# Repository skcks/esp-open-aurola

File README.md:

# esp-open-aurola
light controller board

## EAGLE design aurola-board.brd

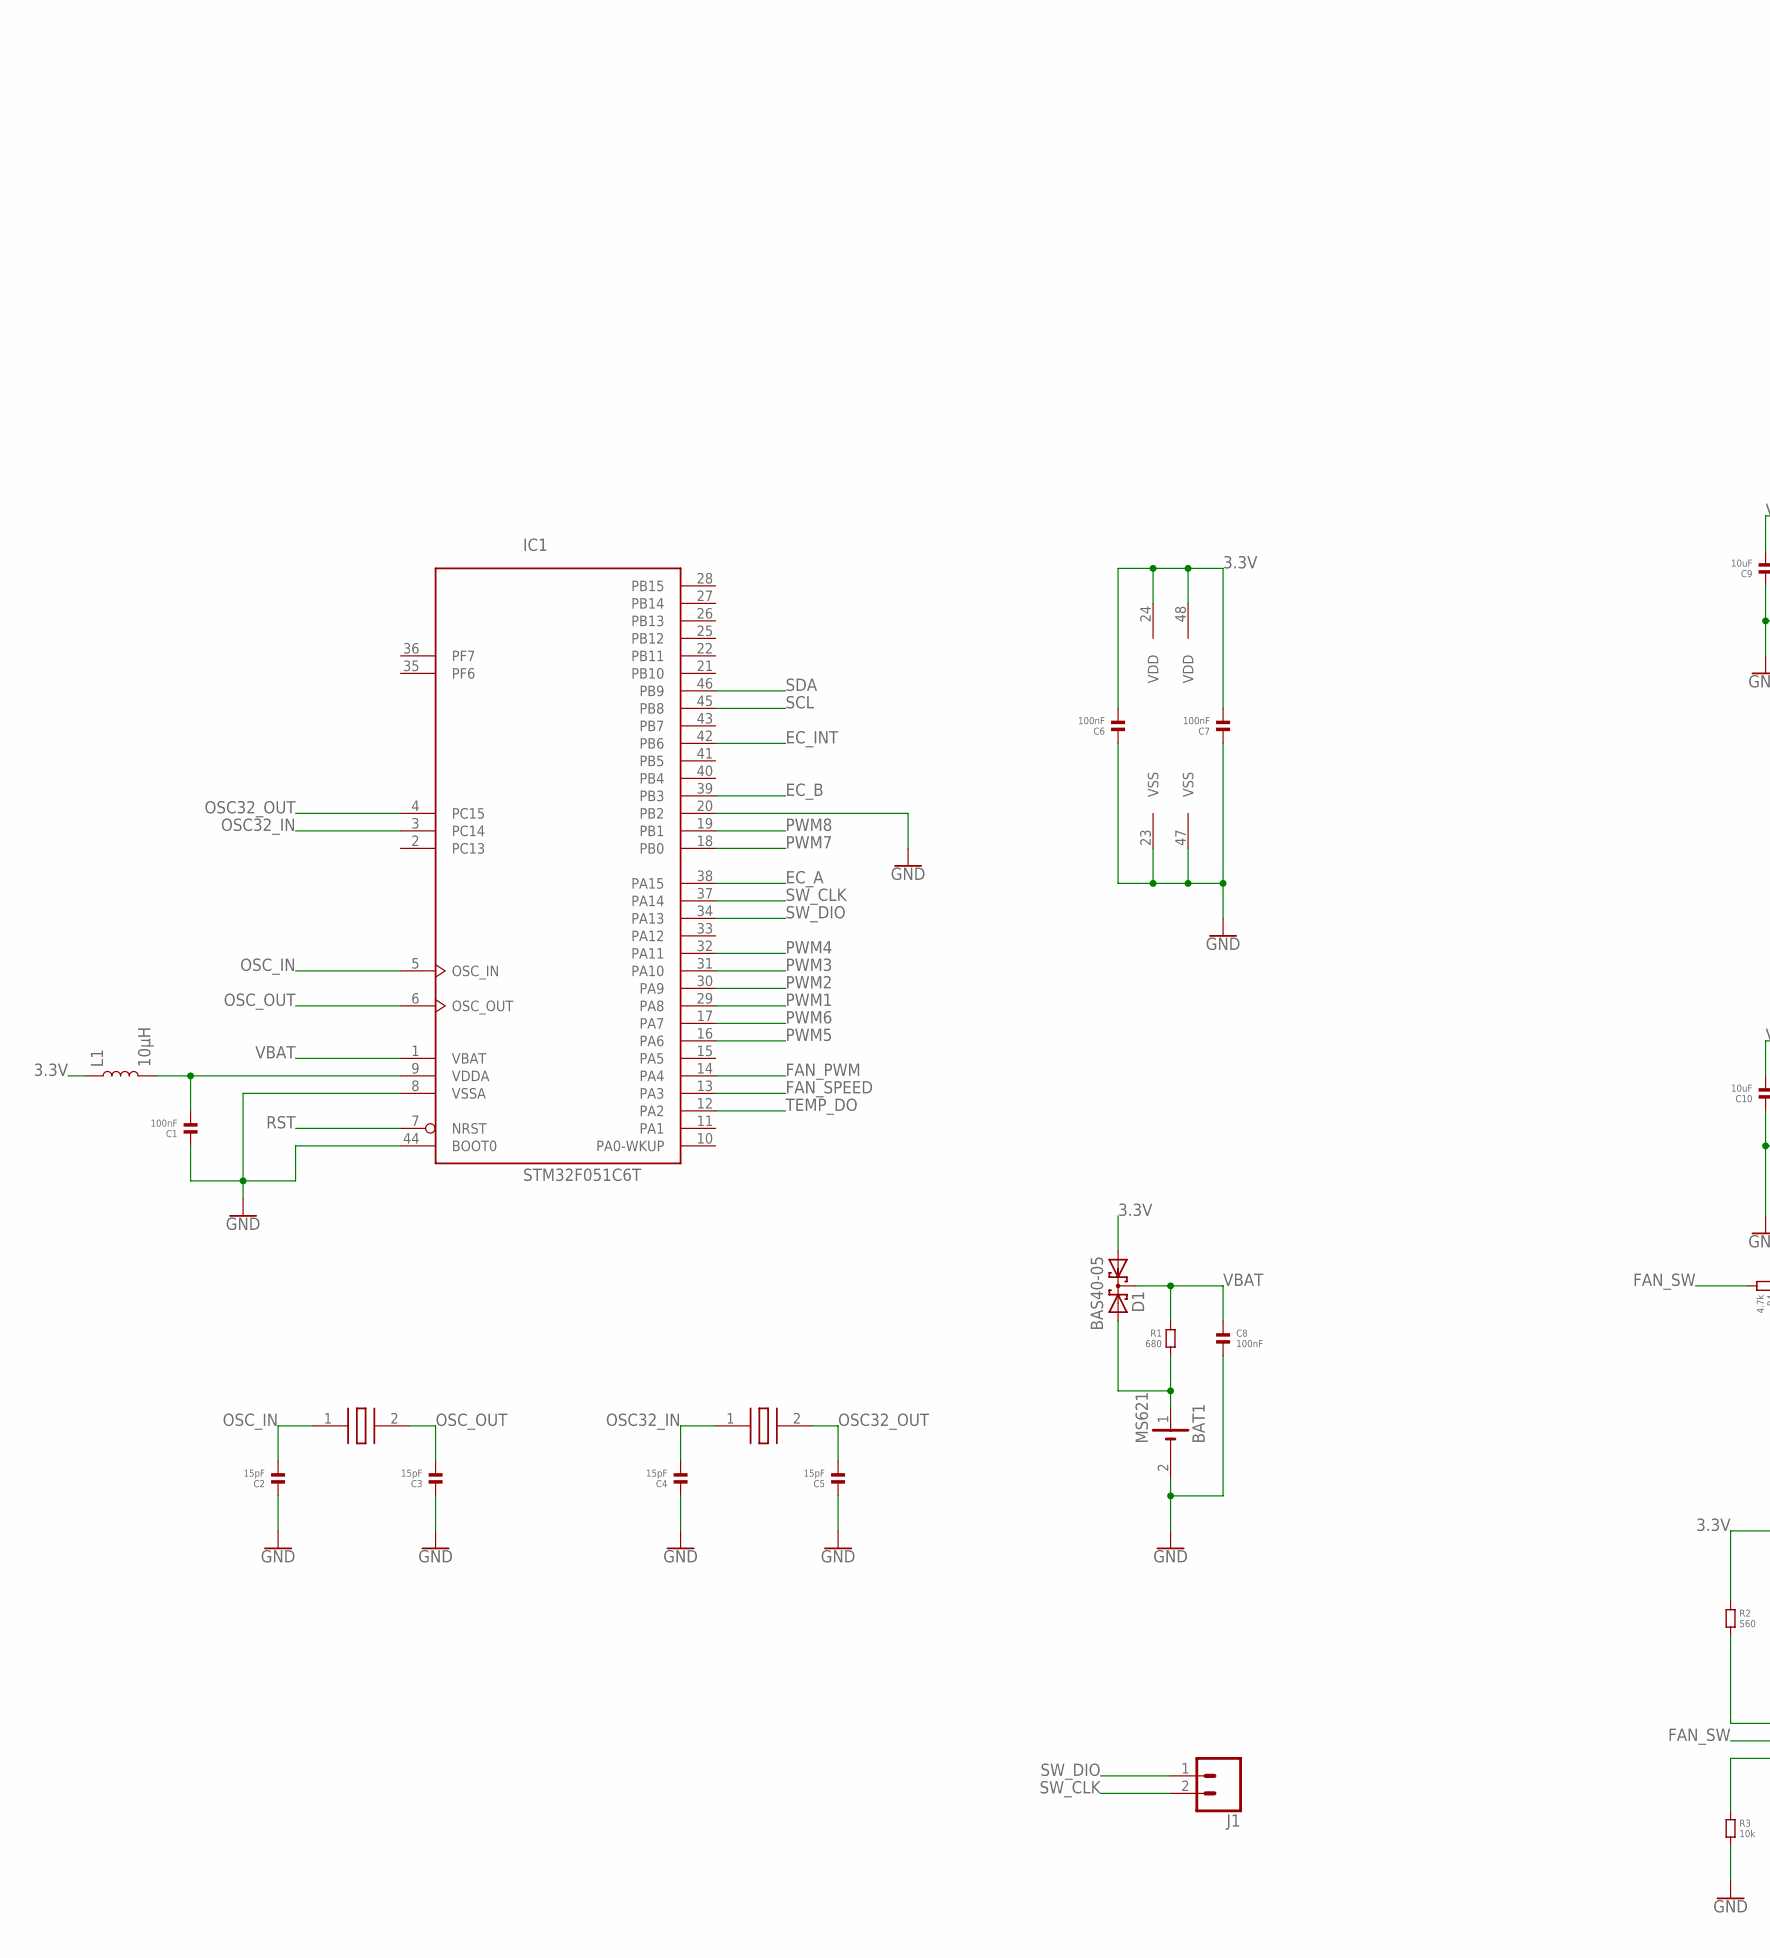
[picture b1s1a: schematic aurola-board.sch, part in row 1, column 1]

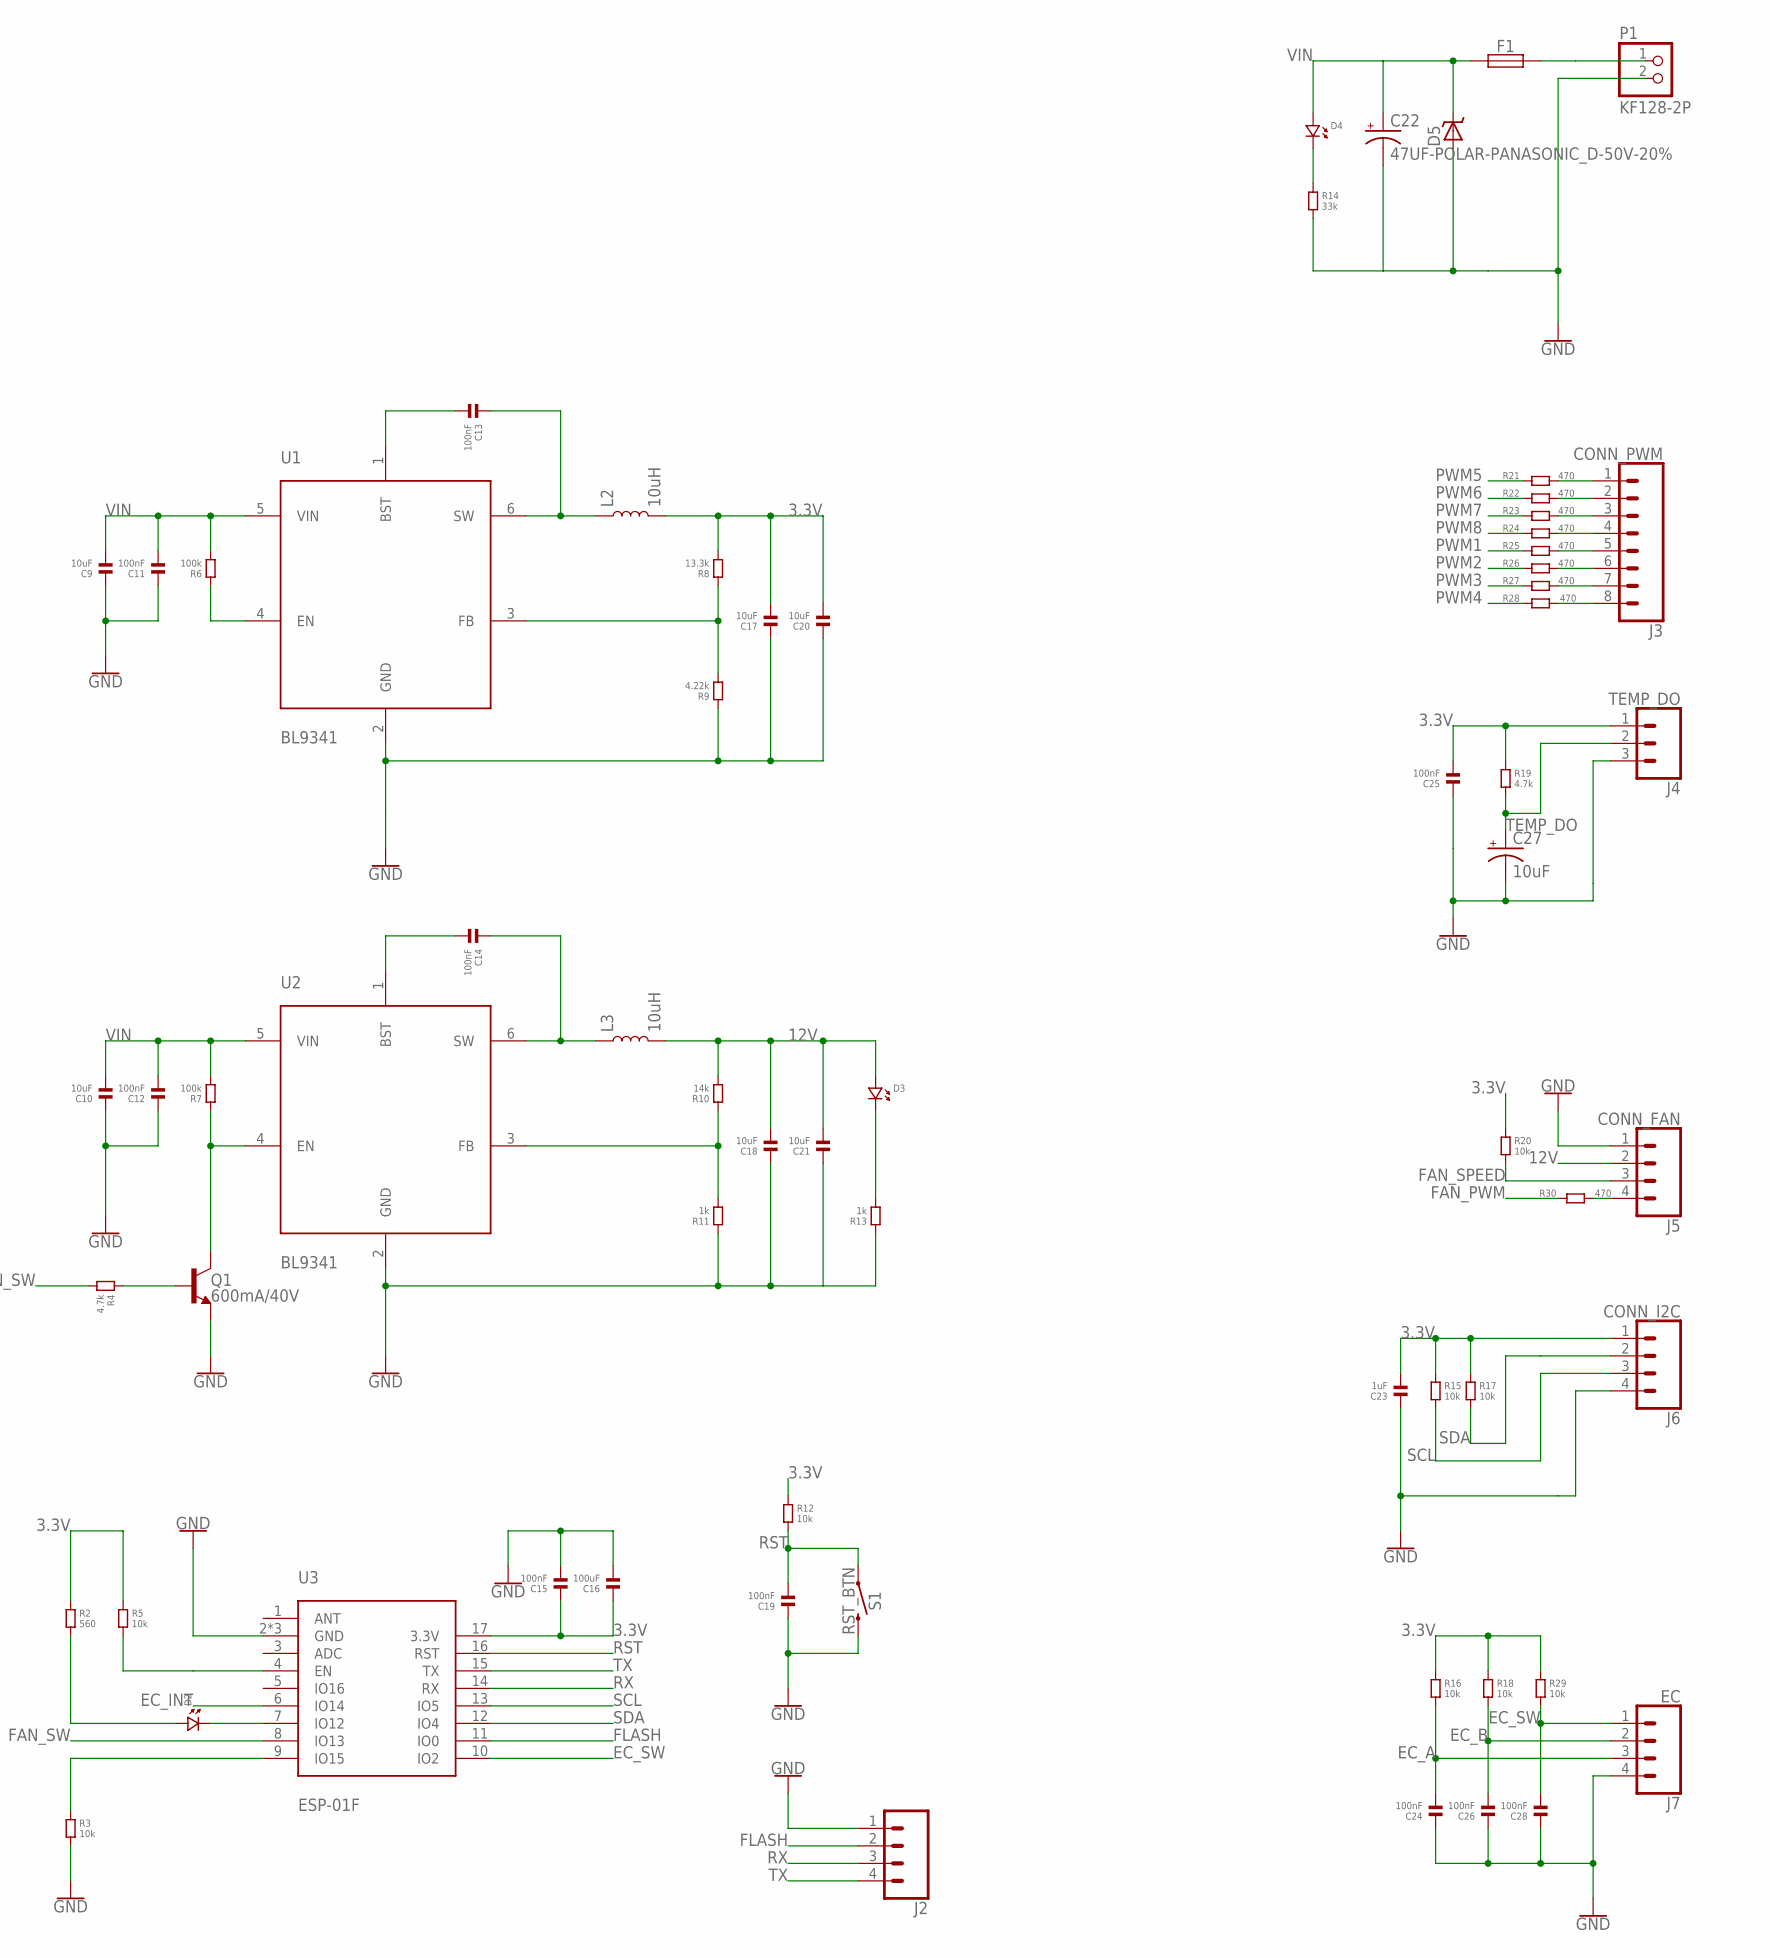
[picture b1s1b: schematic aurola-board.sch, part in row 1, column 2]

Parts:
BAT1: MS621; SMT_BAT
C1, C6, C7, C8, C13, C14, C15, C19, C24, C25, C26, C28: 100nF; 0603
C2, C3, C4, C5: 15pF; 0603
C9, C10, C17, C18, C20, C21: 10uF; 1206
C11, C12: 100nF; 0805
C16: 100uF; 1210
C22: 47UF-POLAR-PANASONIC_D-50V-20%; PANASONIC_D
C23: 1uF; 0603
C27: 10uF; EIA3216
D1: BAS40-05; SOT23
D2, D3, D4: LED.0603; 0603.LED
D5: D_TVS-SMA; SMA_DO214AC
F1: FUSE-1206; C1206
IC1: STM32F051C6T; LQFP48
J1: CONN_02; 1X02
J2: CONN_04; 1X04
J3: CONN_PWM; PH2.0_8P
J4: TEMP_DO; PH2.0_3P
J5: CONN_FAN; PH2.0_4P
J6: CONN_I2C; PH2.0_4P
J7: EC; PH2.0_4P
L1: 10µH; 0805
L2, L3: 10uH; CR54
P1: KF128-2P; 2P-2.54MM
Q1: 600mA/40V; SOT23-3
R1: 680; 0805
R2: 560; 0603
R3, R5, R12, R15, R16, R17, R18, R20, R29: 10k; 0603
R4, R19: 4.7k; 0603
R6, R7: 100k; 0603
R8: 13.3k; 0603
R9: 4.22k; 0603
R10: 14k; 0603
R11, R13: 1k; 0603
R14: 33k; 0603
R21, R22, R23, R24, R25, R26, R27, R28, R30: 470; 0603
S1: RST_BTN; TACTILE_SWITCH_SMD_6.0X3.5MM
U1, U2: BL9341; SOT23-6
U3: ESP-01F
Y1: NX5032CA-8MHZ
Y2: 32.768KHZ-FC-135

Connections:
3.3V: C6.2, C7.2, C15.1, C16.1, C17.2, C20.2, C23.2, C25.2, D1.1 (A1), IC1.24 (VDD), IC1.48 (VDD), J4.1, J6.1, L1.1, L2.P$2 (2), R2.1, R5.1, R8.2, R12.1, R15.1, R16.1, R17.1, R18.1, R19.1, R20.1, R29.1, U3.17 (3.3V)
12V: C18.2, C21.2, D3.P$1 (1), J5.2, L3.P$2 (2), R10.2
EC_A: C24.2, IC1.38 (PA15), J7.3, R16.2
EC_B: C26.2, IC1.39 (PB3), J7.2, R18.2
EC_INT: IC1.42 (PB6), U3.6 (IO14)
EC_SW: C28.2, J7.1, R29.2, U3.10 (IO2)
FAN_PWM: IC1.14 (PA4), R30.1
FAN_SPEED: IC1.13 (PA3), J5.3, R20.2
FAN_SW: R4.2, U3.8 (IO13)
FLASH: J2.2, U3.11 (IO0)
GND: BAT1.2 (-), C1.1, C2.1, C3.1, C4.1, C5.1, C6.1, C7.1, C8.2, C9.1, C10.1, C11.1, C12.1, C15.2, C16.2, C17.1, C18.1, C19.1, C20.1, C21.1, C22.-, C23.1, C24.1, C25.1, C26.1, C27.-, C28.1, D5.A, IC1.8 (VSSA), IC1.20 (PB2), IC1.23 (VSS), IC1.44 (BOOT0), IC1.47 (VSS), J2.1, J4.3, J5.1, J6.4, J7.4, P1.2, Q1.2 (E), R3.2, R9.1, R11.1, R13.1, R14.2, S1.2, U1.2 (GND), U2.2 (GND), U3.2 (GND), U3.18 (GND), U3.19 (GND)
unnamed: Q1.3 (C), R7.1, U2.4 (EN)
unnamed: C13.1, L2.P$1 (1), U1.6 (SW)
unnamed: R6.1, U1.4 (EN)
unnamed: R8.1, R9.2, U1.3 (FB)
unnamed: R10.1, R11.2, U2.3 (FB)
unnamed: C14.1, L3.P$1 (1), U2.6 (SW)
unnamed: C14.2, U2.1 (BST)
unnamed: C13.2, U1.1 (BST)
unnamed: J3.1, R21.2
unnamed: J3.2, R22.2
unnamed: J3.3, R23.2
unnamed: J3.4, R24.2
unnamed: J3.5, R25.2
unnamed: J3.6, R26.2
unnamed: J3.7, R27.2
unnamed: J3.8, R28.2
unnamed: R5.2, U3.4 (EN)
unnamed: J5.4, R30.2
unnamed: R3.1, U3.9 (IO15)
unnamed: Q1.1 (B), R4.1
unnamed: BAT1.1 (+), D1.2 (A2), R1.2
unnamed: C1.2, IC1.9 (VDDA), L1.2
unnamed: D2.P$2 (2), U3.7 (IO12)
unnamed: D2.P$1 (1), R2.2
unnamed: F1.2, P1.1
unnamed: D4.P$2 (2), R14.1
unnamed: D3.P$2 (2), R13.2
OSC32_IN: C4.2, IC1.3 (PC14), Y2.1 (1.XIN)
OSC32_OUT: C5.2, IC1.4 (PC15), Y2.2 (2.XIN)
OSC_IN: C2.2, IC1.5 (OSC_IN), Y1.1 (1.XIN)
OSC_OUT: C3.2, IC1.6 (OSC_OUT), Y1.2 (2.XOUT)
PWM1: IC1.29 (PA8), R25.1
PWM2: IC1.30 (PA9), R26.1
PWM3: IC1.31 (PA10), R27.1
PWM4: IC1.32 (PA11), R28.1
PWM5: IC1.16 (PA6), R21.1
PWM6: IC1.17 (PA7), R22.1
PWM7: IC1.18 (PB0), R23.1
PWM8: IC1.19 (PB1), R24.1
RST: C19.2, IC1.7 (NRST), R12.2, S1.1, U3.16 (RST)
RX: J2.3, U3.14 (RX)
SCL: IC1.45 (PB8), J6.3, R15.2, U3.13 (IO5)
SDA: IC1.46 (PB9), J6.2, R17.2, U3.12 (IO4)
SW_CLK: IC1.37 (PA14), J1.2
SW_DIO: IC1.34 (PA13), J1.1
TEMP_DO: C27.+, IC1.12 (PA2), J4.2, R19.2
TX: J2.4, U3.15 (TX)
VBAT: C8.1, D1.3 (K1K2), IC1.1 (VBAT), R1.1
VIN: C9.2, C10.2, C11.2, C12.2, C22.+, D4.P$1 (1), D5.C, F1.1, R6.2, R7.2, U1.5 (VIN), U2.5 (VIN)

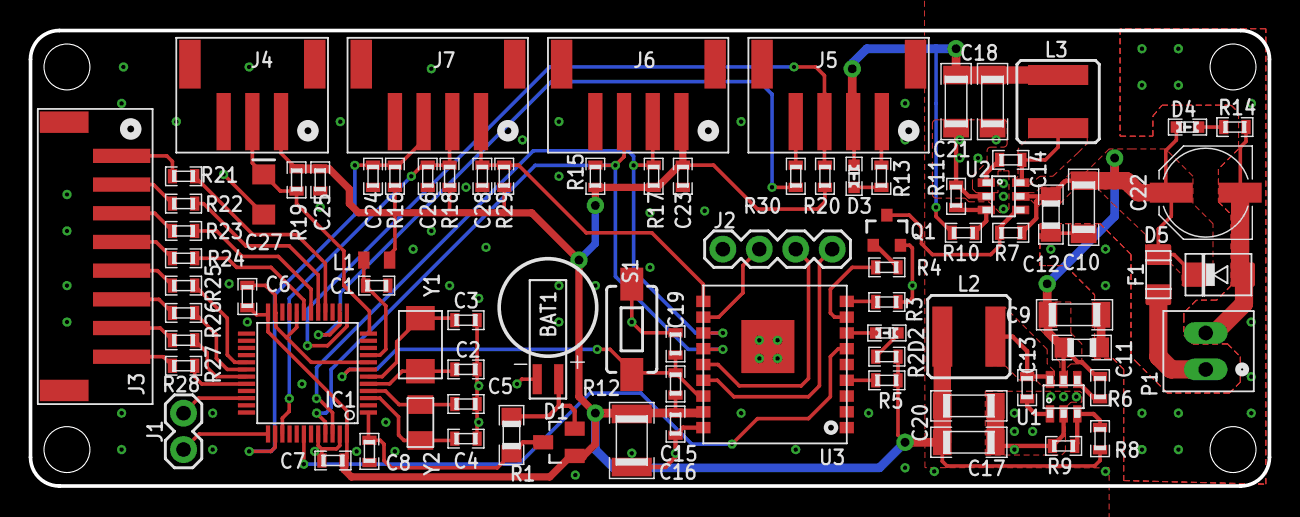
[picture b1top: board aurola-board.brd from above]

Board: 2 copper layers, 86.4 x 31.8 mm, 84 parts (0 on the bottom side), 60 nets.

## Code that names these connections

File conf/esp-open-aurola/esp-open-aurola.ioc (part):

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Mcu.Name=STM32F031C(4-6)Tx
Mcu.Package=LQFP48
Mcu.UserName=STM32F031C6Tx
PA10.GPIOParameters=GPIO_Label
PA10.GPIO_Label=PWM3
PA10.Signal=S_TIM1_CH3
PA11.GPIOParameters=GPIO_Label
PA11.GPIO_Label=PWM4
PA11.Signal=S_TIM1_CH4
PA13.Mode=Serial_Wire
PA13.Signal=SYS_SWDIO
PA14.Mode=Serial_Wire
PA14.Signal=SYS_SWCLK
PA15.GPIOParameters=GPIO_Label
PA15.GPIO_Label=EC_A
PA15.Signal=S_TIM2_CH1_ETR
PA2.GPIOParameters=GPIO_PuPd,GPIO_Label,GPIO_Mode
PA2.GPIO_Label=TEMP_DO
PA2.GPIO_Mode=GPIO_MODE_INPUT
PA2.GPIO_PuPd=GPIO_PULLUP
PA2.Signal=GPIO_Input
PA3.GPIOParameters=GPIO_PuPd,GPIO_Label,GPIO_ModeDefaultOutputPP
PA3.GPIO_Label=REC_ACTIVE
PA3.GPIO_ModeDefaultOutputPP=GPIO_MODE_OUTPUT_PP
PA3.GPIO_PuPd=GPIO_PULLUP
PA3.Signal=GPIO_Output
PA4.GPIOParameters=GPIO_Label
PA4.GPIO_Label=FAN_PWM
PA4.Signal=S_TIM14_CH1
PA6.GPIOParameters=GPIO_Label
PA6.GPIO_Label=PWM5
PA6.Signal=S_TIM3_CH1
PA7.GPIOParameters=GPIO_Label
PA7.GPIO_Label=PWM6
PA7.Signal=S_TIM3_CH2
PA8.GPIOParameters=GPIO_Label
PA8.GPIO_Label=PWM1
PA8.Signal=S_TIM1_CH1
PA9.GPIOParameters=GPIO_Label
PA9.GPIO_Label=PWM2
PA9.Signal=S_TIM1_CH2
PB0.GPIOParameters=GPIO_Label
PB0.GPIO_Label=PWM7
PB0.Signal=S_TIM3_CH3
PB1.GPIOParameters=GPIO_Label
PB1.GPIO_Label=PWM8
PB1.Signal=S_TIM3_CH4
PB3.GPIOParameters=GPIO_Label
PB3.GPIO_Label=EC_B
PB3.Signal=S_TIM2_CH2
PB8.Mode=I2C
PB8.Signal=I2C1_SCL
PB9.Mode=I2C
PB9.Signal=I2C1_SDA
PC14-OSC32_IN.Mode=LSE-External-Oscillator
PC14-OSC32_IN.Signal=RCC_OSC32_IN
PC15-OSC32_OUT.Mode=LSE-External-Oscillator
PC15-OSC32_OUT.Signal=RCC_OSC32_OUT
PF0-OSC_IN.Mode=HSE-External-Oscillator
PF0-OSC_IN.Signal=RCC_OSC_IN
PF1-OSC_OUT.Mode=HSE-External-Oscillator
PF1-OSC_OUT.Signal=RCC_OSC_OUT
RCC.SYSCLKFreq_VALUE=48000000
RCC.SYSCLKSource=RCC_SYSCLKSOURCE_PLLCLK
board=custom

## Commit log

2018-07-16 initialize pcb project
2018-07-17 完成布局
2018-07-18 调整丝印位置
2018-07-18 轻微调整布线
2018-07-18 输出打样文件
2018-07-18 调整丝印
2018-07-18 调整敷铜
2018-07-18 微调线路

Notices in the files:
parts and their libraries:
SparkFun-Coils: Licensing: Creative Commons ShareAlike 4.0 International - https://creativecommons.org/licenses/by-sa/4.0
